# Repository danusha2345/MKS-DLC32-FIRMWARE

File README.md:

# MKS-DLC32-FIRMWARE — CNC-форк с TMC2209 по UART

Прошивка контроллера **MKS DLC32 v2.1** (ESP32) для ЧПУ-станка со шпинделем:
**без экрана**, с драйверами **TMC2209 в UART-режиме** — ток, микрошаг и тихий
StealthChop настраиваются командами по USB/Wi-Fi, без перемычек и подстроечников.

Форк ветки `MKS-DLC32-NEW-CNC` от [IDLEVEL/MKS-DLC32-FIRMWARE](https://github.com/IDLEVEL/MKS-DLC32-FIRMWARE),
которая основана на брошенной официальной прошивке
[makerbase-mks/MKS-DLC32-FIRMWARE](https://github.com/makerbase-mks/MKS-DLC32-FIRMWARE)
(движок Grbl_ESP32 v1.1). Прошивка переведена на **arduino-esp32 2.0.17**
(espressif32 6.12.0, ESP-IDF 4.4.7) с серией фиксов стабильности — разбор в
[`docs/MIGRATION_6X.md`](docs/MIGRATION_6X.md), технические заметки форка — в
[`docs/FORK_NOTES.md`](docs/FORK_NOTES.md).

## Конфигурация этой ветки

- **Экран не используется.** Станок управляется по USB, Telnet, WebUI в браузере
  или Android-приложением — панель TS35 в этой конфигурации не нужна.
- **TMC2209 по UART**: общая шина на пинах разъёма I2C платы. Из-за этого:
  - выходы **coolant M7/M8 недоступны** (их пины заняты шиной);
  - **внешний пульт IDLEVEL несовместим** с этим вариантом (использует те же IO0/IO4);
  - нужна небольшая **навесная обвязка согласования уровней** (логика драйверов на
    плате пятивольтовая) — см. ниже.
- Шаги идут как обычно (step/dir через I2S-регистры): UART нужен только для
  настройки, при потере связи с драйвером движение не останавливается.

## Целевое железо

- Плата: **MKS DLC32 v2.1** — ESP32-WROOM-32U (8 МБ flash, 520 КБ RAM), степперы
  через I2S-сдвиговые регистры. Полная спека — [`docs/BOARD_SPEC.md`](docs/BOARD_SPEC.md).
- Драйверы: 3× **TMC2209** (степстики) в сокетах платы.
- Назначение: **ЧПУ-фрезер** (3 оси XYZ, шпиндель с PWM).

Карта пинов задаётся в `Firmware/Grbl_Esp32/src/Machines/i2s_out_xyz_mks_dlc32.h`
(флаги `USE_BOARD_V2_0` + `USR_Z_MOTOR` + `USE_TMC2209_UART`):

| Функция | Пин |
|---|---|
| Шпиндель PWM | GPIO32 |
| Probe | GPIO22 |
| Концевики X / Y / Z | GPIO36 / GPIO35 / GPIO34 |
| Степперы X/Y/Z (step/dir) | I2S (BCK16 / WS17 / DATA21) |
| Шина TMC2209 UART | TX=IO0, RX=IO4 (пины разъёма I2C) |
| SD-карта | SPI: SCK14, MISO12, MOSI13, CS15; детект GPIO39 |

Все 3 оси полноценные (движение/джоггинг/probe/обнуление по Z работают).
Авто-хоминг по Z выключен в дефолтах (`$22=0`) — включается через настройки или
`DEFAULT_HOMING_ENABLE 1` + `DEFAULT_HOMING_CYCLE_1 (bit(Z_AXIS))`.

## TMC2209: подключение и настройка

Коротко (полная инструкция с номиналами и граблями —
[`docs/TMC2209_UART.md`](docs/TMC2209_UART.md)):

- ⚠️ **Напрямую проводом подключать нельзя.** На DLC32 логика шаговой части
  пятивольтовая: VIO степстика (пин 7 сокета) жёстко разведён на **+5V**,
  step/dir/en приходят с 74HC595, запитанного 5 В, а EN ещё и подтянут к +5V
  резисторами R31–R33. У TMC2209 порог «1» равен `0.7 × VIO` = **3.5 В** (3.3 В
  с ESP32 недостаточно), а отвечает он уровнем VIO = 5 В — прямо в GPIO ESP32,
  у которого абсолютный максимум ~3.6 В. Нужен преобразователь уровней на одной
  UART-линии: два копеечных буфера с фиксированным направлением (`SN74AHCT1G125`
  с питанием 5 В на TX и `SN74LVC1G17` с питанием 3.3 В на RX — у последнего вход
  толерантен к 5.5 В), либо один `TXU0202`. Плату при этом переделывать не надо.
  Разбор всех вариантов (в том числе почему не годится «перевести VIO на 3.3 В»
  и почему нельзя понизить сам источник 5 В) —
  в [`docs/TMC2209_UART.md`](docs/TMC2209_UART.md).

  ```text
  разъём I2C DLC32                                       общая линия PDN_UART
  (1=+3V3, 2=GND, 3=SDA=IO0, 4=SCL=IO4)
                     ┌────────────────────────┐
   SDA = IO0 (TX) ──►│ SN74AHCT1G125, VCC=+5В │──[1 кОм]──┐
                     │ OE# → GND              │           │
                     └────────────────────────┘           ├───────┬────────┬────────┐
                     ┌────────────────────────┐           │       │        │        │
   SCL = IO4 (RX) ◄──│ SN74LVC1G17, VCC=+3.3В │◄──────────┘   PDN_UART PDN_UART PDN_UART
                     └────────────────────────┘               модуль X модуль Y модуль Z
   GND ── общий                                               (пины RST/SLP сокета)
   +5 В для обвязки — с EXP1 (пин 10), экран не используется
  ```

  На разъёме I2C пин питания — **+3V3, не 5 В**; подключать его никуда не нужно.
- PDN_UART у степстиков SilentStepStick v2.0 выведен на позиции сокета
  **RST/SLP**, а DLC32 соединяет эти два пина между собой и больше никуда —
  провод шины паяется прямо к площадке сокета, ножки отгибать не нужно.
- Шина одна на все три драйвера: адрес получателя прошивка вписывает в каждый
  пакет. Адрес задаётся пинами **MS1/MS2** (в UART-режиме это адресные биты, а не
  микрошаг), которые на DLC32 выведены на штатные DIP-переключатели:

  | Драйвер в сокете | Адрес | Поз. 1 (MS1) | Поз. 2 (MS2) | Поз. 3 |
  |---|---|---|---|---|
  | X (`SW1`) | 0 | OFF | OFF | OFF |
  | Y (`SW2`) | 1 | **ON** | OFF | OFF |
  | Z (`SW3`) | 2 | OFF | **ON** | OFF |

  Позиция 3 — это не MS3, а **SPREAD**: включённая даст SpreadCycle вместо
  StealthChop, держать OFF.

  Принадлежность мотора к оси задаёт **сокет** (step/dir), адрес — только кому
  уйдут настройки тока/микрошага. Перепутанный адрес не поменяет оси местами,
  но настройки «для X» молча применятся к чужому мотору, поэтому: драйвер в
  сокете X обвязывается на адрес 0, в Y — 1, в Z — 2. Два одинаковых адреса =
  оба молчат (CRC-ошибки), прошивка сообщит при старте. Проверка раскладки:
  `$X/Current/Run=0.1` → момент должен потерять именно X-мотор; повторить для Y/Z.
- Настройки в прошивке: ток `$X/Current/Run` (серия `$140`), удержание
  `$X/Current/Hold` (`$150`), микрошаг `$X/Microsteps` (`$160`) — аналогично Y/Z.
  Хранятся в NVS, применяются сразу: можно менять хоть перед каждым заданием.
  `$X/Current/Run=0` отключает выход драйвера (TOFF=0); микрошаг принимается
  только из ряда 0/2/4/8/16/32/64/128/256.
- Режим — StealthChop (тихий), задан на этапе компиляции.
- При старте прошивка проверяет связь с каждым драйвером и пишет результат в
  консоль; предупреждает о short-to-ground и перегреве.

> ⚠️ Вариант TMC2209 UART собран и проверен компиляцией, но **на живом станке
> ещё не гонялся** — базовой прошивки это не касается.

## Сборка

Нужен [PlatformIO Core](https://platformio.org/) (или расширение PlatformIO в VS Code).

```bash
cd Firmware
pio run -e mks_dlc32_v2_1_tmc            # сборка TMC-варианта
pio run -e mks_dlc32_v2_1_tmc -t upload  # прошивка по USB
```

Артефакт: `Firmware/.pio/build/mks_dlc32_v2_1_tmc/firmware.bin`.

Окружения (`Firmware/platformio.ini` + `Firmware/ini/mks_dlc32.ini`):

| env | Назначение |
|---|---|
| `mks_dlc32_v2_1_tmc` | **Основное для этой ветки**: TMC2209 по UART. Партиция `esp32_8MiB.csv` (2× OTA-слота по 3 МБ) |
| `mks_dlc32_v2_1` | Базовый вариант без TMC UART (драйверы в обычном step/dir-режиме, coolant на месте) |
| `mks_dlc32_v2_1_ota` | Загрузка по воздуху (espota, IP в `ini/mks_dlc32.ini`). ⚠️ Собирает **базовый** вариант — для OTA TMC-варианта добавьте в env флаг `-D USE_TMC2209_UART` |

Готовые бинарники в [`release/`](release/) (со скриптами `flash_usb.sh`/`.bat`)
тоже собраны из **базового** варианта — TMC-вариант собирайте из исходников.

## Тесты

Чистую логику (без зависимостей от железа) покрываем нативными unit-тестами:

```bash
cd Firmware
pio test -e native
```

Тесты лежат в `Firmware/test/`, чистая логика — в модулях без зависимостей от
железа, чтобы её можно было гонять нативно:

| Модуль | Тесты | Что покрыто |
|---|---|---|
| `src/SDJobPolicy.cpp` | `test_sd_job_policy` | политика «SD-печать + команды со второго интерфейса» |
| `src/SDLineReader.cpp` | `test_sd_line_reader` | разбор строки G-кода: границы буфера, EOF, ошибка чтения |
| `src/Motors/TrinamicSettings.cpp` | `test_trinamic_settings` | микрошаг вне ряда, деление на ноль в `calc_tstep`, нулевой ток |

Всего 23 теста. Драйверы и `readFileLine` остаются тонкими обёртками над этими
модулями — железо в тестах не участвует.

## Статус

Базовая функциональность **проверена на реальной плате MKS DLC32 v2.1**
(ESP32-D0WD, flash 8 МБ) — протокол испытаний в
[`docs/CODE_REVIEW.md`](docs/CODE_REVIEW.md). Проверка велась на голой плате
(USB): пункты, требующие собранного станка — лимиты/хоминг/движение/джоггинг/
probe/SD-печать со «Стоп» — собраны в
[`docs/MIGRATION_6X.md`](docs/MIGRATION_6X.md#-что-надо-протестировать-на-железе).

- ✅ Собирается на Linux/Mac/Windows.
- ✅ Wi-Fi: событийный авто-реконнект STA, self-heal из AP-fallback, mDNS в AP и
  STA (`http://mks-dlc32.local`). Сеть — WPA2 2.4 ГГц (WPA3-only ESP32 не умеет).
  Ping-soak 60 c = 0% потерь.
- ✅ OTA по воздуху: партиция под реальные 8 МБ, два app-слота по 3 МБ.
- ✅ SD ↔ USB/сеть: во время задания с карты со второго интерфейса проходят
  realtime и read-only запросы (`?`, `$$`, `$G`…), движение отклоняется
  `error:120` **без обрыва задания**.
- ✅ WebUI: канал WebUI↔ядро жив, большие ответы не теряются; имя устройства
  `mks-dlc32`, меняется в WebUI.
- ✅ Telnet, HTTP-загрузка файлов на SD (`/upload`). Карта — только FAT32
  (exFAT не монтируется — карты >32 ГБ переформатировать). Во время задания с SD
  загрузка нового файла намеренно блокируется — заливать до запуска.
- ✅ Удалённое управление через центральный сервер: плата сама подключается к
  нему по TCP (`$Remote/Server`, `$Remote/Token`, `$Remote/Name`, хранятся в
  NVS) — инструкция в [`docs/REMOTE_CONTROL.md`](docs/REMOTE_CONTROL.md).
- ✅ SD-задание честно сообщает о сбое: слишком длинная строка (от 255 символов)
  или ошибка чтения больше не выдаются за успешное завершение; устранена запись
  за границу буфера на строке ровно в 255 символов.
- ✅ Read-only команды (`$$`, `$+`, `$L`, `$S`, `$SC`, `$CMD`) переведены на явный
  `anyState`; `$Axis/Current/Run=0` больше не программирует максимальный ток,
  микрошаг принимается только из ряда 0/2/4…256.
- ⏳ TMC2209 UART: собрано, ждёт проверки на железе (см. выше).
- 🔜 По умолчанию аутентификация выключена — смените пароль AP в WebUI.

## Лицензия

GPLv3 (наследуется от Grbl / Grbl_ESP32). См. [`LICENSE`](LICENSE).

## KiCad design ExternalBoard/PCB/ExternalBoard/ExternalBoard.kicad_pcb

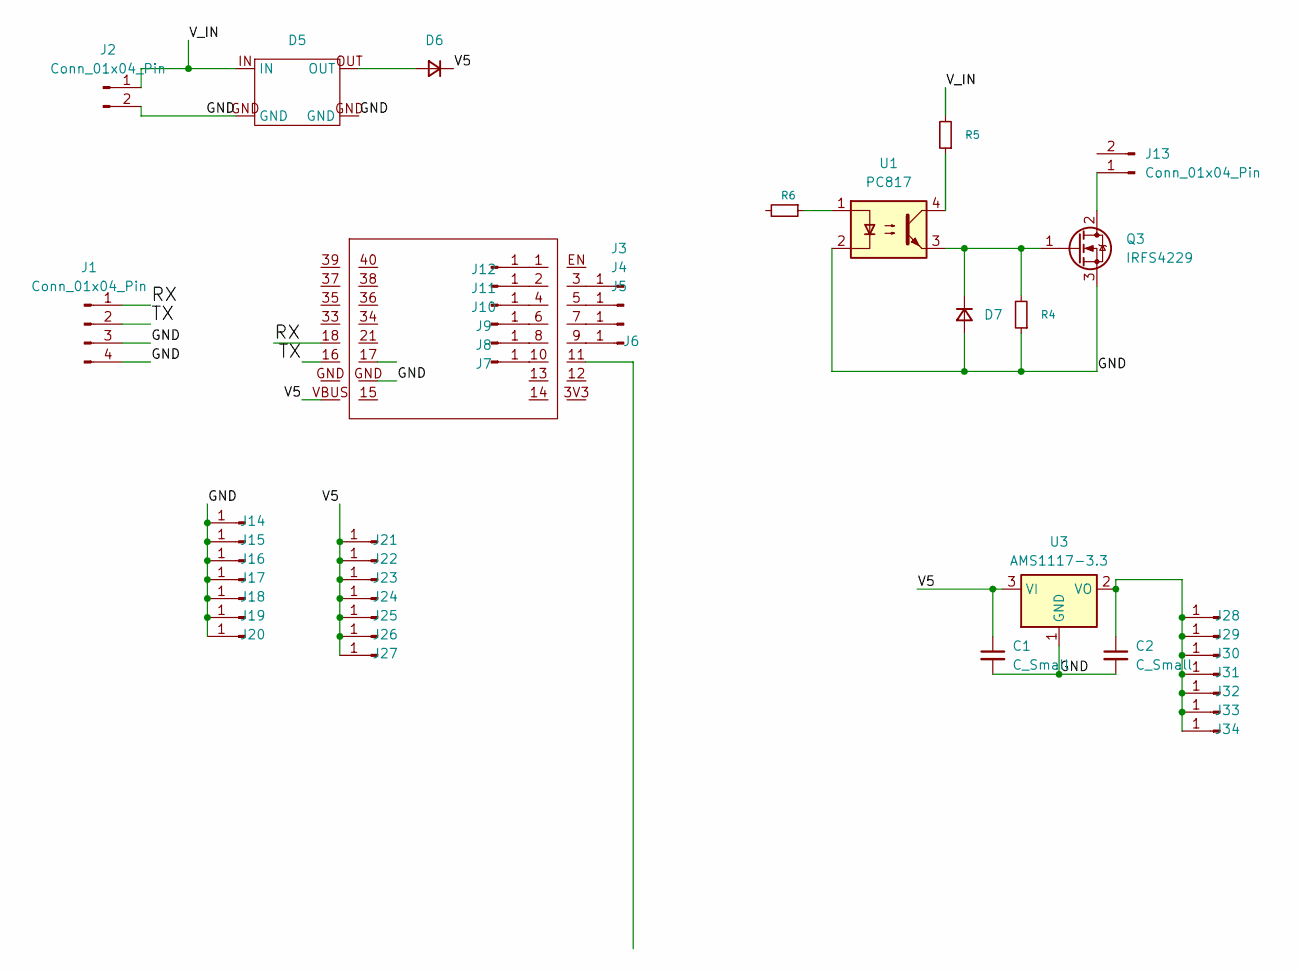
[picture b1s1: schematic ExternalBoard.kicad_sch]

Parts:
C1, C2: C_Small; C_1206_3216Metric
D1: ESP32_S2_V2
D5: StepDown
D6: D_Small; D_SMA
D7: D_Small; D_SMF
J1: Conn_01x04_Pin; PinHeader_1x04_P2.54mm_Vertical
J2, J13: Conn_01x04_Pin; PinHeader_1x02_P2.54mm_Vertical
J3, J4, J5, J6, J7, J8, J9, J10, J11, J12, J14, J15, J16, J17, J18, J19, J20, J21, J22, J23, J24, J25, J26, J27, J28, J29, J30, J31, J32, J33, J34: Conn_01x04_Pin; PIN0
Q3: IRFS4229; TO-263-2
R4, R5, R6: R_Small; R_1206_3216Metric_Pad1.30x1.75mm_HandSolder
U1: PC817; DIP-4_W7.62mm
U3: AMS1117-3.3; SOT-223-3_TabPin2

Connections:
/GND: C1.2, C2.2, D1.GND, D5.GND, D7.2 (A), J1.3, J1.4, J2.2, J14.1 (Pin_1_1), J15.1 (Pin_1_1), J16.1 (Pin_1_1), J17.1 (Pin_1_1), J18.1 (Pin_1_1), J19.1 (Pin_1_1), J20.1 (Pin_1_1), Q3.3 (S), R4.1, U1.2, U3.1 (GND)
/RX: D1.18, J1.1
/TX: D1.16, J1.2
/V5: C1.1, D1.VBUS, D6.1 (K), J21.1 (Pin_1_1), J22.1 (Pin_1_1), J23.1 (Pin_1_1), J24.1 (Pin_1_1), J25.1 (Pin_1_1), J26.1 (Pin_1_1), J27.1 (Pin_1_1), U3.3 (VI)
/V_IN: D5.IN, J2.1, R5.2
unnamed: D5.OUT, D6.2 (A)
unnamed: D7.1 (K), Q3.1 (G), R4.2, U1.3
unnamed: D1.3, J3.1 (Pin_1_1)
unnamed: D1.5, J4.1 (Pin_1_1)
unnamed: D1.7, J5.1 (Pin_1_1)
unnamed: D1.9, J6.1 (Pin_1_1)
unnamed: D1.10, J7.1 (Pin_1_1)
unnamed: D1.8, J8.1 (Pin_1_1)
unnamed: D1.6, J9.1 (Pin_1_1)
unnamed: D1.4, J10.1 (Pin_1_1)
unnamed: D1.2, J11.1 (Pin_1_1)
unnamed: D1.1, J12.1 (Pin_1_1)
unnamed: J13.1 (Pin_1_1), Q3.2 (D)
unnamed: C2.1, J28.1 (Pin_1_1), J29.1 (Pin_1_1), J30.1 (Pin_1_1), J31.1 (Pin_1_1), J32.1 (Pin_1_1), J33.1 (Pin_1_1), J34.1 (Pin_1_1), U3.2 (VO)
unnamed: R5.1, U1.4
unnamed: R6.1, U1.1

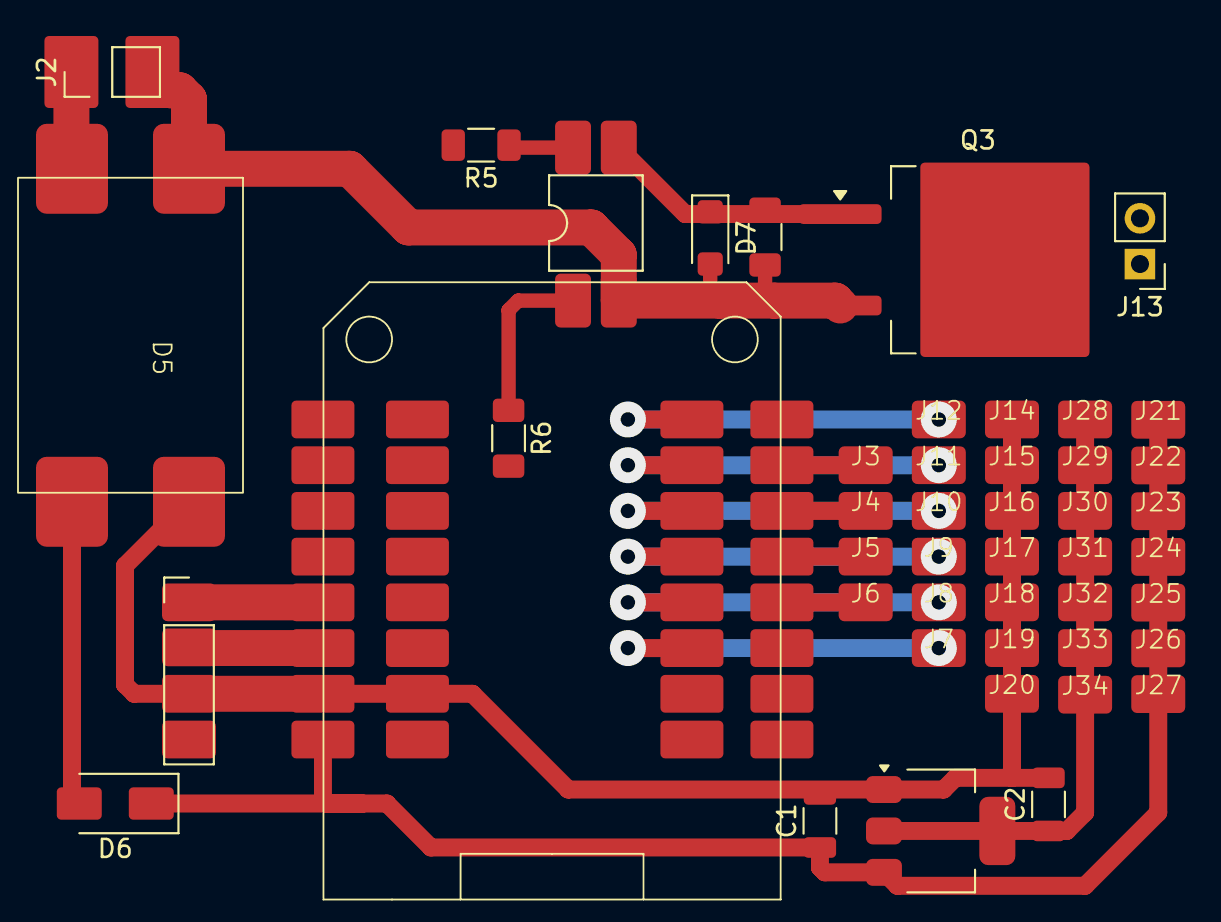
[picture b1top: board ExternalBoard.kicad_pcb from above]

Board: 2 copper layers, 46 parts (0 on the bottom side), 21 nets.

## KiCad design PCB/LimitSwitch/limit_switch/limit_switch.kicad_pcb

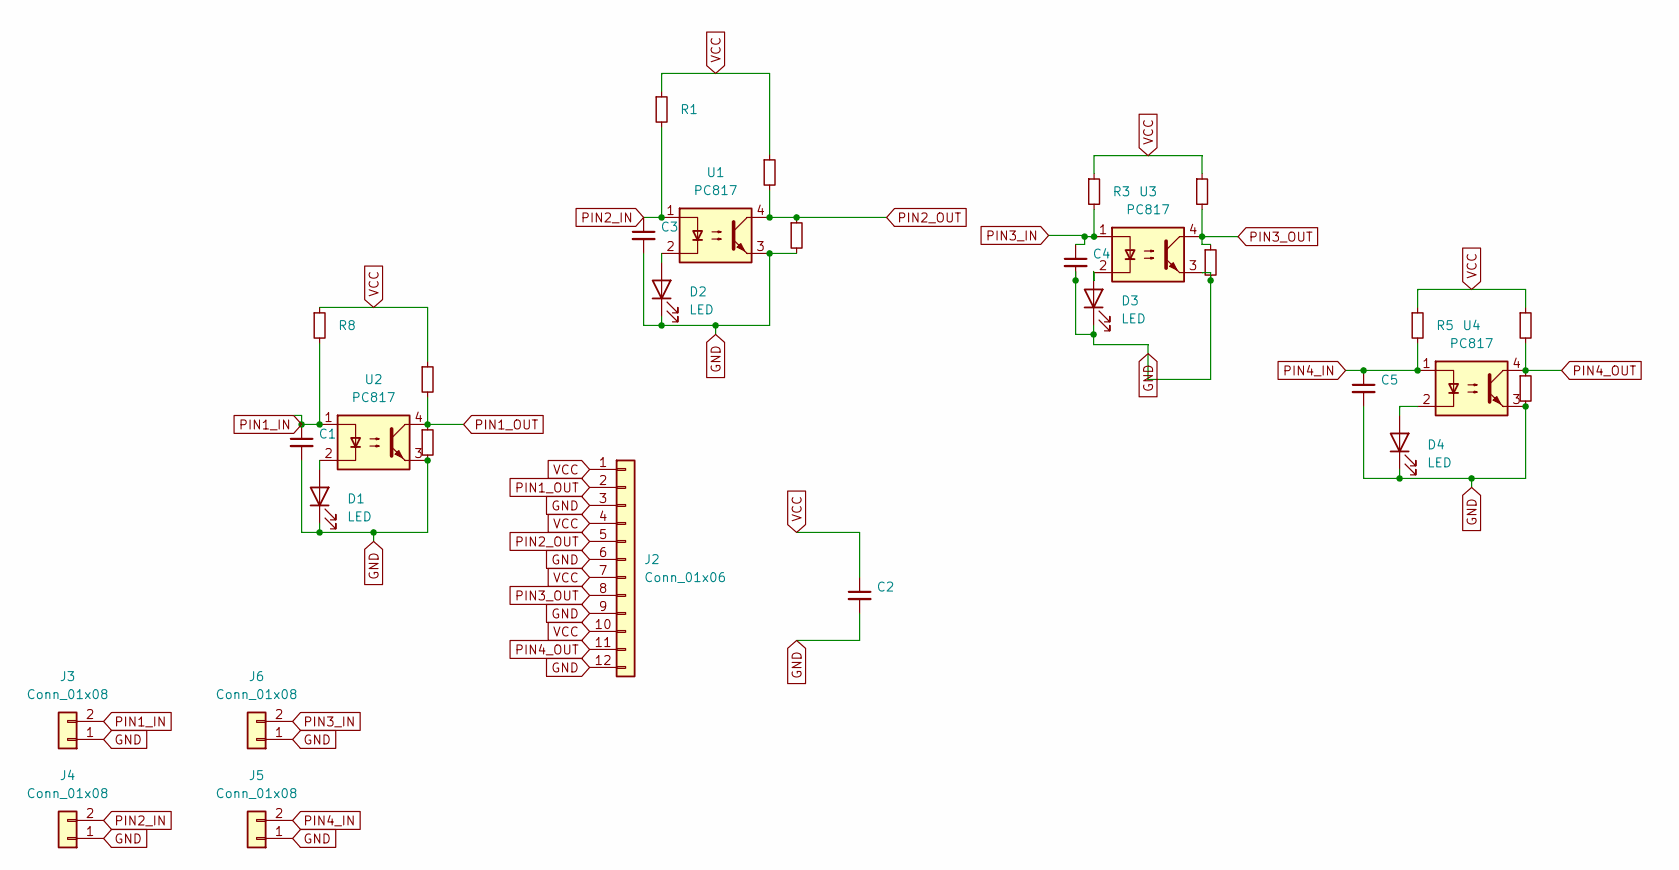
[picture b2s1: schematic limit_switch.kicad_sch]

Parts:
C1, C2, C3, C4, C5: C_Small; C_1206_3216Metric_Pad1.33x1.80mm_HandSolder
D1, D2, D3, D4: LED; R_0805_2012Metric_Pad1.20x1.40mm_HandSolder
J2: Conn_01x06; PinHeader_1x12_P2.54mm_Vertical
J3, J4, J5, J6: Conn_01x08; PinHeader_1x02_P2.54mm_Vertical
R1, R2, R3, R4, R5, R6, R7, R8, R9, R10, R11, R12: R_Small; R_1206_3216Metric_Pad1.30x1.75mm_HandSolder
U1, U2, U3, U4: PC817; DIP-4_W8.89mm_SMDSocket_LongPads

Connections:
GND: C1.2, C2.2, C3.2, C4.2, C5.2, D1.1 (K), D2.1 (K), D3.1 (K), D4.1 (K), J2.3, J2.6, J2.9, J2.12, J3.1, J4.1, J5.1, J6.1, R7.2, R10.2, R11.2, R12.2, U1.3, U2.3, U3.3, U4.3
unnamed: D1.2 (A), U2.2
unnamed: D2.2 (A), U1.2
unnamed: D3.2 (A), U3.2
unnamed: D4.2 (A), U4.2
PIN1_IN: C1.1, J3.2, R8.2, U2.1
PIN1_OUT: J2.2, R9.2, R12.1, U2.4
PIN2_IN: C3.1, J4.2, R1.2, U1.1
PIN2_OUT: J2.5, R2.2, R7.1, U1.4
PIN3_IN: C4.1, J6.2, R3.2, U3.1
PIN3_OUT: J2.8, R4.2, R10.1, U3.4
PIN4_IN: C5.1, J5.2, R5.2, U4.1
PIN4_OUT: J2.11, R6.2, R11.1, U4.4
VCC: C2.1, J2.1, J2.4, J2.7, J2.10, R1.1, R2.1, R3.1, R4.1, R5.1, R6.1, R8.1, R9.1

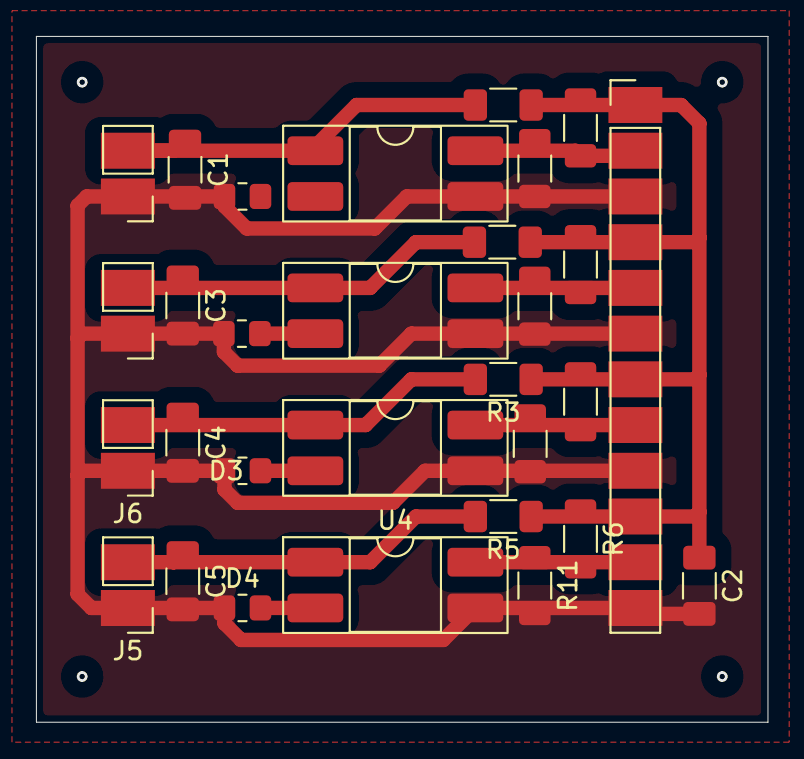
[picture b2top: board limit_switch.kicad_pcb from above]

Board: 2 copper layers, 40.6 x 38.1 mm, 30 parts (0 on the bottom side), 14 nets.

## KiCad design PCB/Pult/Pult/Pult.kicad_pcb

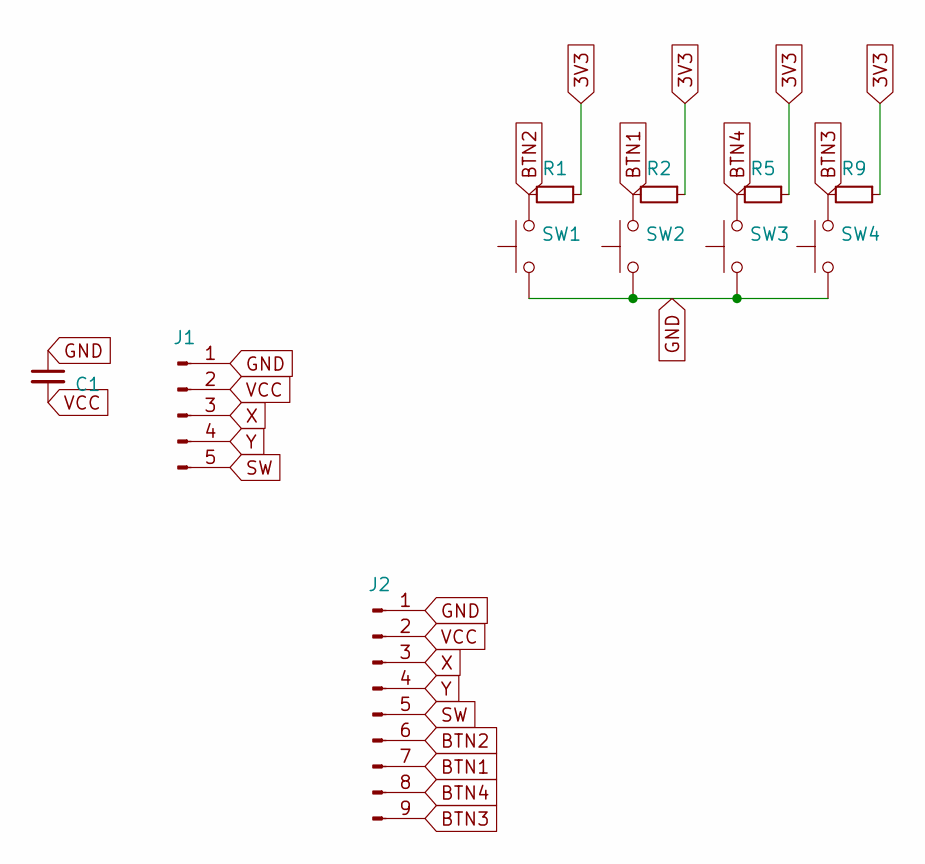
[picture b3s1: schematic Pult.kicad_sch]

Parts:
C1: C_Small; C_1206_3216Metric_Pad1.33x1.80mm_HandSolder
J1: Conn_01x04_Pin; PinHeader_1x05_P2.54mm_Vertical
J2: Conn_01x04_Pin; PinHeader_1x09_P2.54mm_Vertical
R1, R2, R5, R9: R_Small; R_1206_3216Metric_Pad1.30x1.75mm_HandSolder
SW1, SW2, SW3, SW4: SW_Push; SW_PUSH-12mm

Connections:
3V3: R1.1, R2.1, R5.1, R9.1
BTN1: J2.7, R2.2, SW2.2
BTN2: J2.6, R1.2, SW1.2
BTN3: J2.9, R9.2, SW4.2
BTN4: J2.8, R5.2, SW3.2
GND: C1.1, J1.1, J2.1, SW1.1, SW2.1, SW3.1, SW4.1
SW: J1.5, J2.5
VCC: C1.2, J1.2, J2.2
X: J1.3, J2.3
Y: J1.4, J2.4

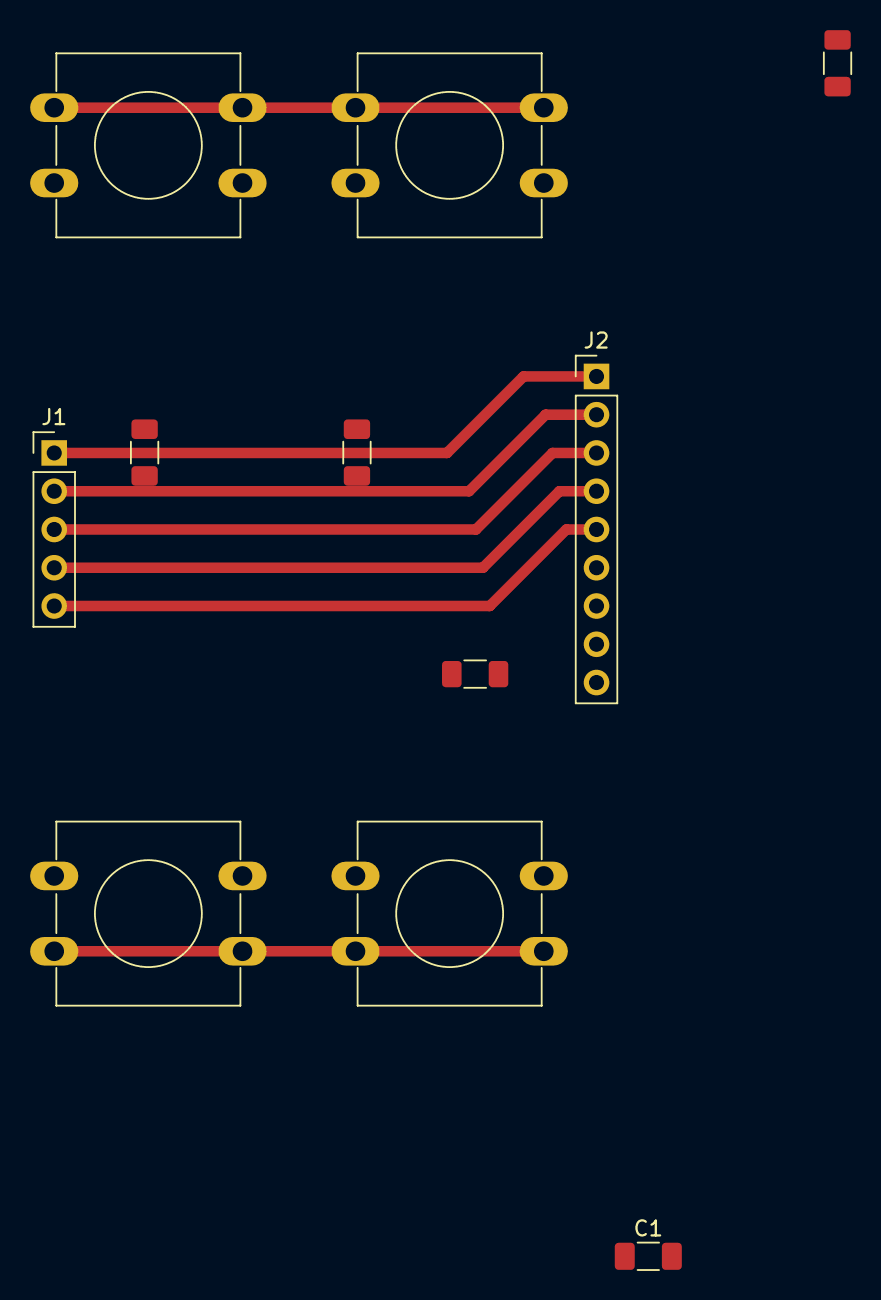
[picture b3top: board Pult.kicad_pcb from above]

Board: 2 copper layers, 11 parts (0 on the bottom side), 10 nets.

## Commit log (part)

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2026-03-23 123333
